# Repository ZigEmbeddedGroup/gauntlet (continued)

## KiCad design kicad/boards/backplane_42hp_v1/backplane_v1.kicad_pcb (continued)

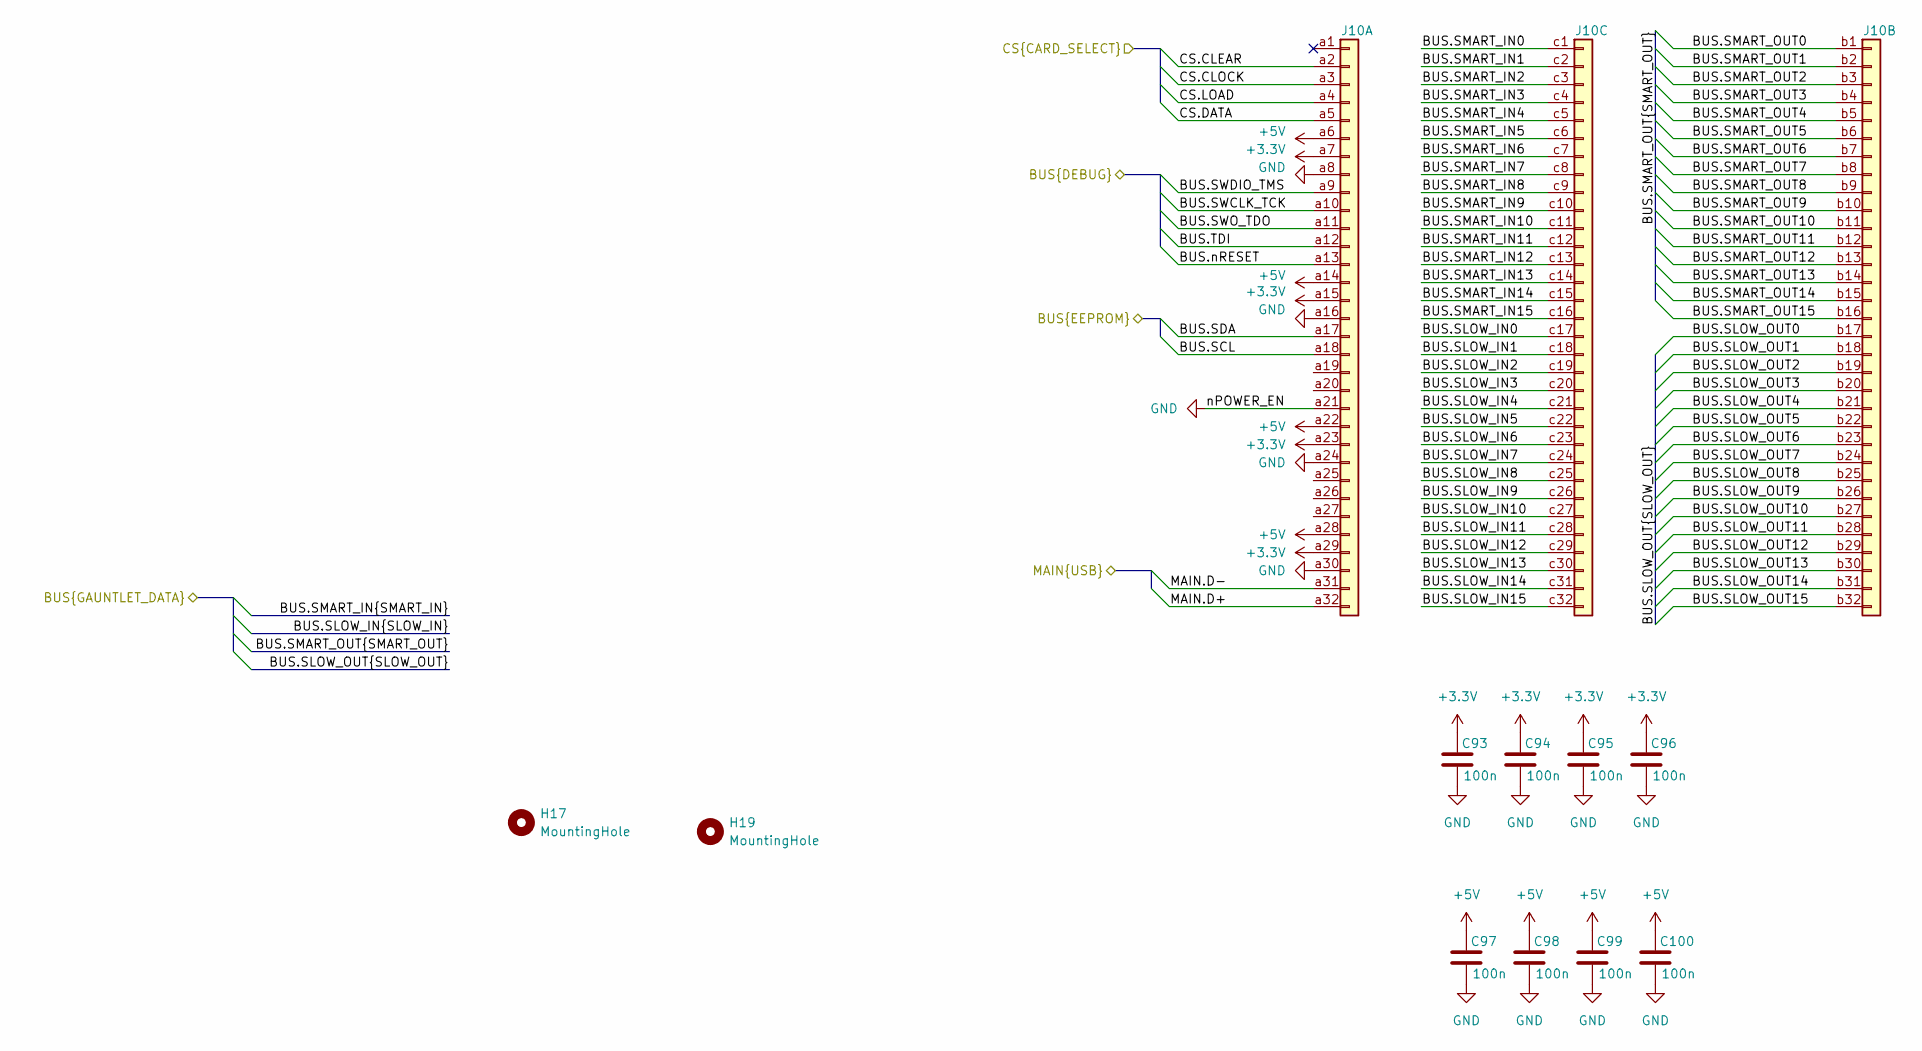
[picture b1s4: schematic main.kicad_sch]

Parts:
C93, C94, C95, C96, C97, C98, C99, C100: 100n; C_0603_1608Metric
H17, H19: MountingHole; MountingHole_3.2mm_M3
J10: DIN41612_03x32_C_Split; DIN41612_C_3x32_Female_Vertical_THT

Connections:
+3.3V: C93.1, C94.1, C95.1, C96.1, J10.a7, J10.a15, J10.a23, J10.a29; also elsewhere on the board
+5V: C97.1, C98.1, C99.1, C100.1, J10.a6, J10.a14, J10.a22, J10.a28; also elsewhere on the board
/BUS.SCL: J10.a18; also elsewhere on the board
/BUS.SDA: J10.a17; also elsewhere on the board
/BUS.SLOW_IN0: J10.c17; also elsewhere on the board
/BUS.SLOW_IN1: J10.c18; also elsewhere on the board
/BUS.SLOW_IN2: J10.c19; also elsewhere on the board
/BUS.SLOW_IN3: J10.c20; also elsewhere on the board
/BUS.SLOW_IN4: J10.c21; also elsewhere on the board
/BUS.SLOW_IN5: J10.c22; also elsewhere on the board
/BUS.SLOW_IN6: J10.c23; also elsewhere on the board
/BUS.SLOW_IN7: J10.c24; also elsewhere on the board
/BUS.SLOW_IN8: J10.c25; also elsewhere on the board
/BUS.SLOW_IN9: J10.c26; also elsewhere on the board
/BUS.SLOW_IN10: J10.c27; also elsewhere on the board
/BUS.SLOW_IN11: J10.c28; also elsewhere on the board
/BUS.SLOW_IN12: J10.c29; also elsewhere on the board
/BUS.SLOW_IN13: J10.c30; also elsewhere on the board
/BUS.SLOW_IN14: J10.c31; also elsewhere on the board
/BUS.SLOW_IN15: J10.c32; also elsewhere on the board
/BUS.SLOW_OUT0: J10.b17; also elsewhere on the board
/BUS.SLOW_OUT1: J10.b18; also elsewhere on the board
/BUS.SLOW_OUT2: J10.b19; also elsewhere on the board
/BUS.SLOW_OUT3: J10.b20; also elsewhere on the board
/BUS.SLOW_OUT4: J10.b21; also elsewhere on the board
/BUS.SLOW_OUT5: J10.b22; also elsewhere on the board
/BUS.SLOW_OUT6: J10.b23; also elsewhere on the board
/BUS.SLOW_OUT7: J10.b24; also elsewhere on the board
/BUS.SLOW_OUT8: J10.b25; also elsewhere on the board
/BUS.SLOW_OUT9: J10.b26; also elsewhere on the board
/BUS.SLOW_OUT10: J10.b27; also elsewhere on the board
/BUS.SLOW_OUT11: J10.b28; also elsewhere on the board
/BUS.SLOW_OUT12: J10.b29; also elsewhere on the board
/BUS.SLOW_OUT13: J10.b30; also elsewhere on the board
/BUS.SLOW_OUT14: J10.b31; also elsewhere on the board
/BUS.SLOW_OUT15: J10.b32; also elsewhere on the board
/BUS.SMART_IN0: J10.c1; also elsewhere on the board
/BUS.SMART_IN1: J10.c2; also elsewhere on the board
/BUS.SMART_IN2: J10.c3; also elsewhere on the board
/BUS.SMART_IN3: J10.c4; also elsewhere on the board
/BUS.SMART_IN4: J10.c5; also elsewhere on the board
/BUS.SMART_IN5: J10.c6; also elsewhere on the board
/BUS.SMART_IN6: J10.c7; also elsewhere on the board
/BUS.SMART_IN7: J10.c8; also elsewhere on the board
/BUS.SMART_IN8: J10.c9; also elsewhere on the board
/BUS.SMART_IN9: J10.c10; also elsewhere on the board
/BUS.SMART_IN10: J10.c11; also elsewhere on the board
/BUS.SMART_IN11: J10.c12; also elsewhere on the board
/BUS.SMART_IN12: J10.c13; also elsewhere on the board
/BUS.SMART_IN13: J10.c14; also elsewhere on the board
/BUS.SMART_IN14: J10.c15; also elsewhere on the board
/BUS.SMART_IN15: J10.c16; also elsewhere on the board
/BUS.SMART_OUT0: J10.b1; also elsewhere on the board
/BUS.SMART_OUT1: J10.b2; also elsewhere on the board
/BUS.SMART_OUT2: J10.b3; also elsewhere on the board
/BUS.SMART_OUT3: J10.b4; also elsewhere on the board
/BUS.SMART_OUT4: J10.b5; also elsewhere on the board
/BUS.SMART_OUT5: J10.b6; also elsewhere on the board
/BUS.SMART_OUT6: J10.b7; also elsewhere on the board
/BUS.SMART_OUT7: J10.b8; also elsewhere on the board
/BUS.SMART_OUT8: J10.b9; also elsewhere on the board
/BUS.SMART_OUT9: J10.b10; also elsewhere on the board
/BUS.SMART_OUT10: J10.b11; also elsewhere on the board
/BUS.SMART_OUT11: J10.b12; also elsewhere on the board
/BUS.SMART_OUT12: J10.b13; also elsewhere on the board
/BUS.SMART_OUT13: J10.b14; also elsewhere on the board
/BUS.SMART_OUT14: J10.b15; also elsewhere on the board
/BUS.SMART_OUT15: J10.b16; also elsewhere on the board
/BUS.SWCLK_TCK: J10.a10; also elsewhere on the board
/BUS.SWDIO_TMS: J10.a9; also elsewhere on the board
/BUS.SWO_TDO: J10.a11; also elsewhere on the board
/BUS.TDI: J10.a12; also elsewhere on the board
/BUS.nRESET: J10.a13; also elsewhere on the board
/CS.CLEAR: J10.a2; also elsewhere on the board
/CS.CLOCK: J10.a3; also elsewhere on the board
/CS.DATA: J10.a5; also elsewhere on the board
/CS.LOAD: J10.a4; also elsewhere on the board
/MAIN.D+: J10.a32; also elsewhere on the board
/MAIN.D-: J10.a31; also elsewhere on the board
GND: C93.2, C94.2, C95.2, C96.2, C97.2, C98.2, C99.2, C100.2, J10.a8, J10.a16, J10.a21, J10.a24, J10.a30; also elsewhere on the board

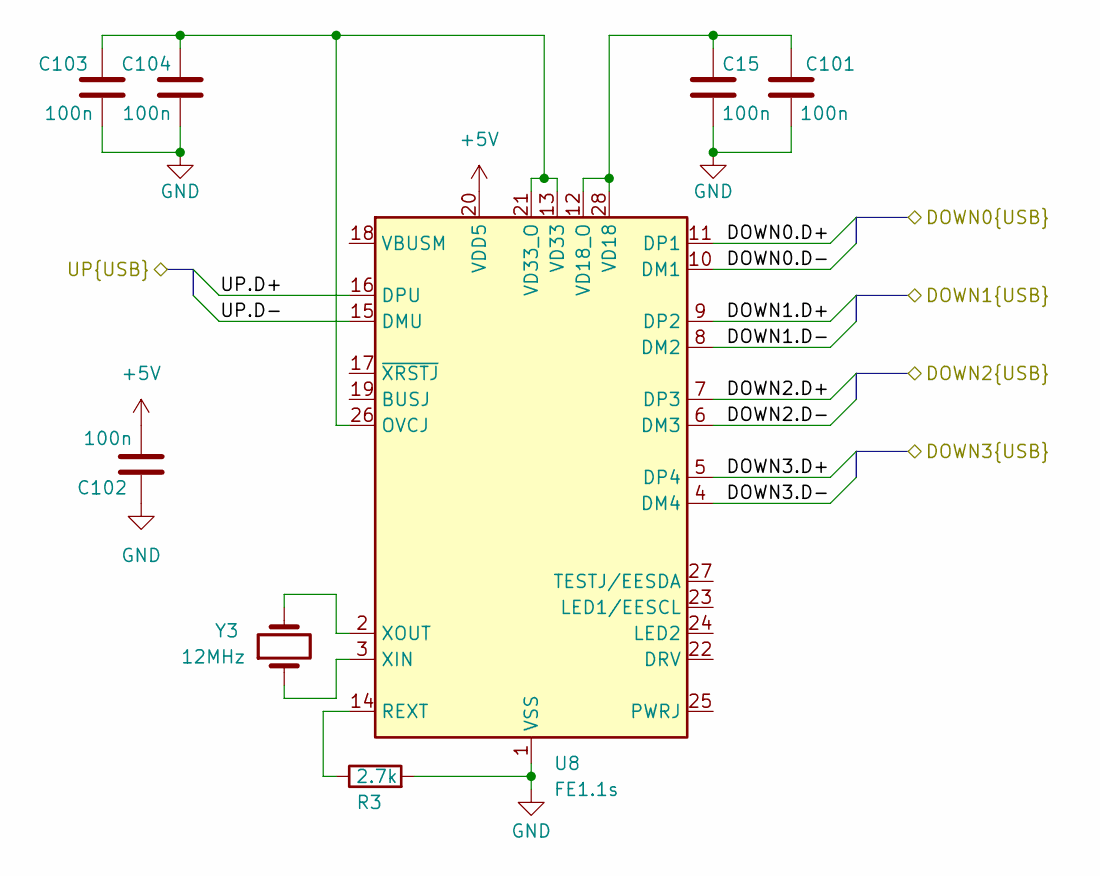
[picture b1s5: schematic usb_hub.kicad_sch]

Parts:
C15, C101, C102, C103, C104: 100n
R3: 2.7k
U8: FE1.1s; SSOP-28_3.9x9.9mm_P0.635mm
Y3: 12MHz

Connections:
+5V: C102.1, U8.20 (VDD5); also elsewhere on the board
/MAIN.D+: U8.16 (DPU); also elsewhere on the board
/MAIN.D-: U8.15 (DMU); also elsewhere on the board
/USB Hubs/USB Hub/DOWN0.D+: U8.11 (DP1); also elsewhere on the board
/USB Hubs/USB Hub/DOWN0.D-: U8.10 (DM1); also elsewhere on the board
/USB Hubs/USB Hub/DOWN1.D+: U8.9 (DP2); also elsewhere on the board
/USB Hubs/USB Hub/DOWN1.D-: U8.8 (DM2); also elsewhere on the board
/USB Hubs/USB Hub/DOWN2.D+: U8.7 (DP3)
/USB Hubs/USB Hub/DOWN2.D-: U8.6 (DM3)
/USB Hubs/USB Hub/DOWN3.D+: U8.5 (DP4)
/USB Hubs/USB Hub/DOWN3.D-: U8.4 (DM4)
GND: C15.1, C101.1, C102.2, C103.1, C104.1, R3.2, U8.1 (VSS); also elsewhere on the board
unnamed: U8.13 (VD33), U8.21 (VD33_O), U8.26 (OVCJ)
unnamed: U8.12 (VD18_O), U8.28 (VD18)

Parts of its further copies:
U9, U10: FE1.1s; SSOP-28_3.9x9.9mm_P0.635mm

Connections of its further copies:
+5V: U9.20 (VDD5), U10.20 (VDD5); also elsewhere on the board
/USB0.D+: U9.5 (DP4); also elsewhere on the board
/USB0.D-: U9.4 (DM4); also elsewhere on the board
/USB1.D+: U9.7 (DP3); also elsewhere on the board
/USB1.D-: U9.6 (DM3); also elsewhere on the board
/USB2.D+: U9.9 (DP2); also elsewhere on the board
/USB2.D-: U9.8 (DM2); also elsewhere on the board
/USB3.D+: U9.11 (DP1); also elsewhere on the board
/USB3.D-: U9.10 (DM1); also elsewhere on the board
/USB4.D+: U10.5 (DP4); also elsewhere on the board
/USB4.D-: U10.4 (DM4); also elsewhere on the board
/USB5.D+: U10.7 (DP3); also elsewhere on the board
/USB5.D-: U10.6 (DM3); also elsewhere on the board
/USB6.D+: U10.9 (DP2); also elsewhere on the board
/USB6.D-: U10.8 (DM2); also elsewhere on the board
/USB7.D+: U10.11 (DP1); also elsewhere on the board
/USB7.D-: U10.10 (DM1); also elsewhere on the board
/USB Hubs/USB Hub/DOWN0.D+: U9.16 (DPU); also elsewhere on the board
/USB Hubs/USB Hub/DOWN0.D-: U9.15 (DMU); also elsewhere on the board
/USB Hubs/USB Hub/DOWN1.D+: U10.16 (DPU); also elsewhere on the board
/USB Hubs/USB Hub/DOWN1.D-: U10.15 (DMU); also elsewhere on the board
GND: U9.1 (VSS), U10.1 (VSS); also elsewhere on the board
unnamed: U9.13 (VD33), U9.21 (VD33_O), U9.26 (OVCJ)
unnamed: U9.12 (VD18_O), U9.28 (VD18)
unnamed: U10.13 (VD33), U10.21 (VD33_O), U10.26 (OVCJ)
unnamed: U10.12 (VD18_O), U10.28 (VD18)

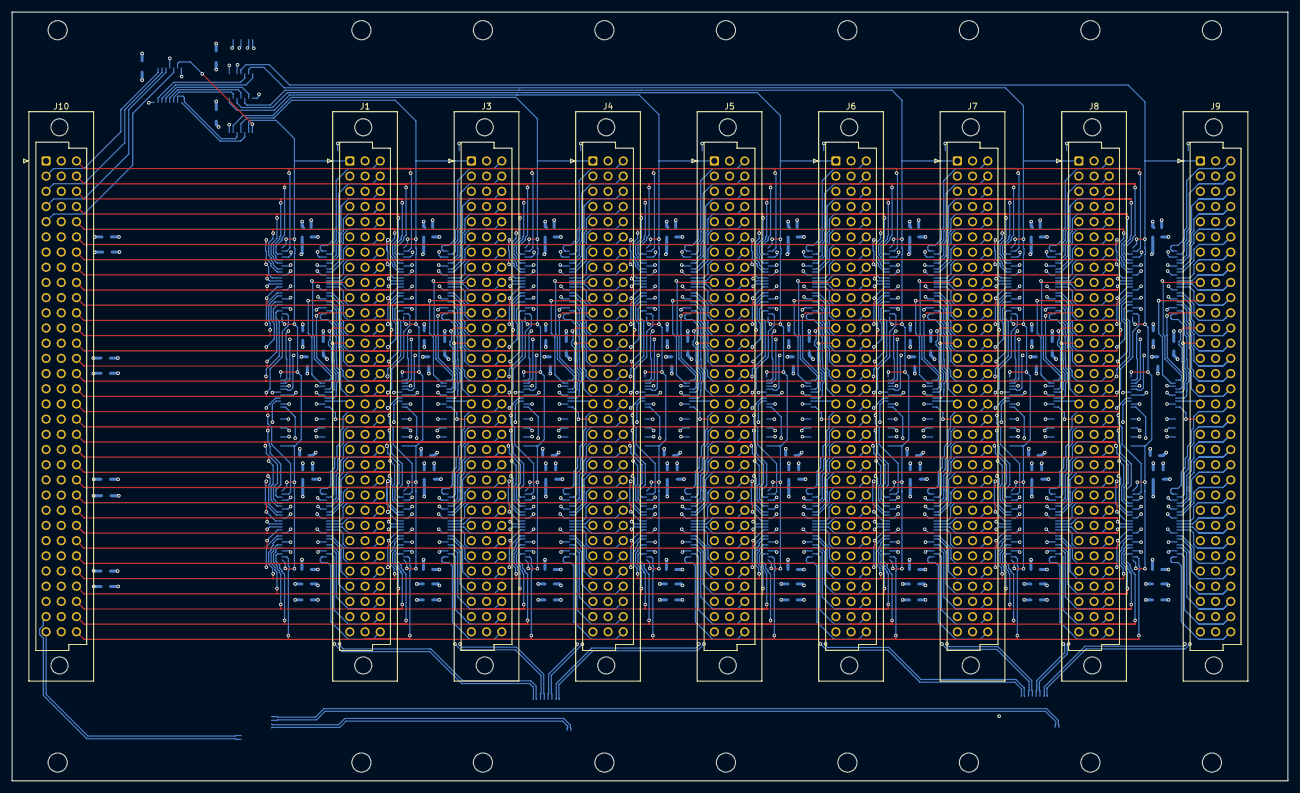
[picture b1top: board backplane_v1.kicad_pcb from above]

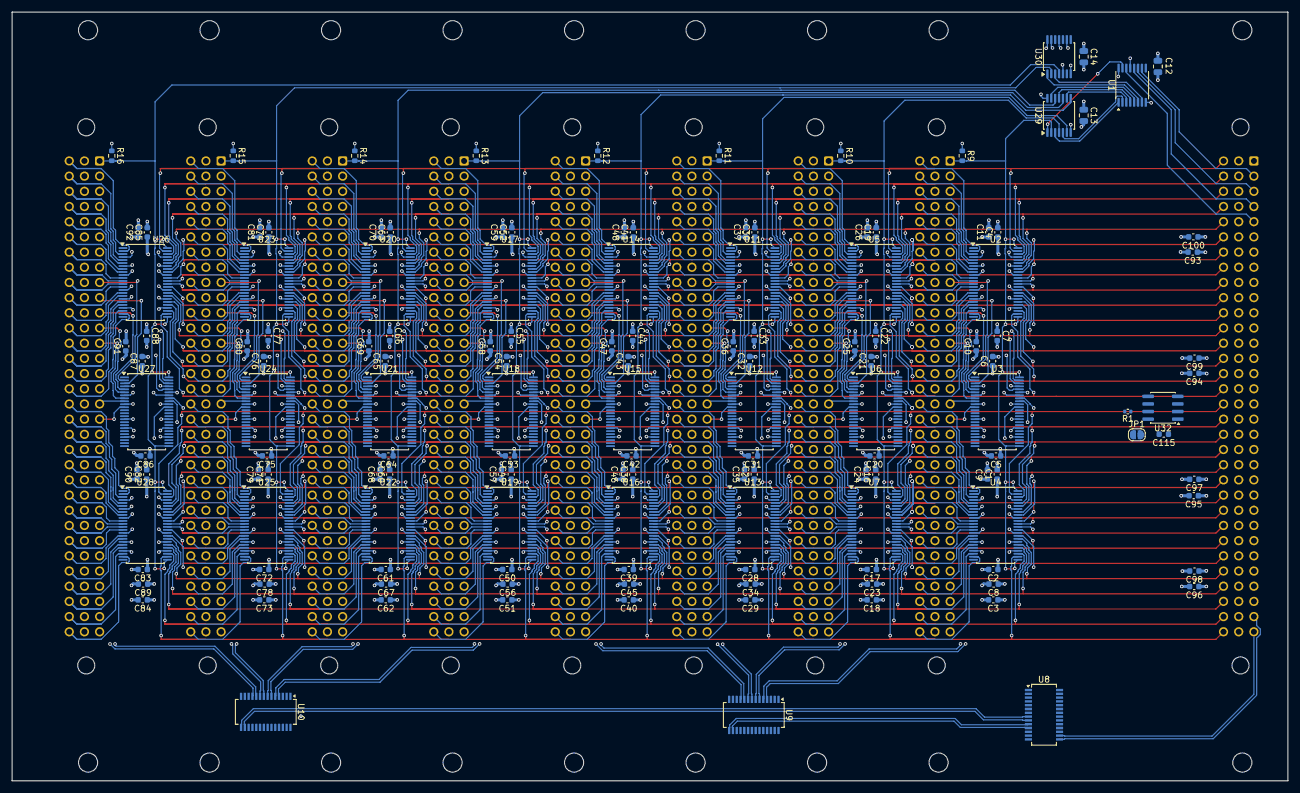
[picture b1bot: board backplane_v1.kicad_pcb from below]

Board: 6 copper layers, 213.4 x 128.6 mm, 168 parts (141 on the bottom side), 435 nets.

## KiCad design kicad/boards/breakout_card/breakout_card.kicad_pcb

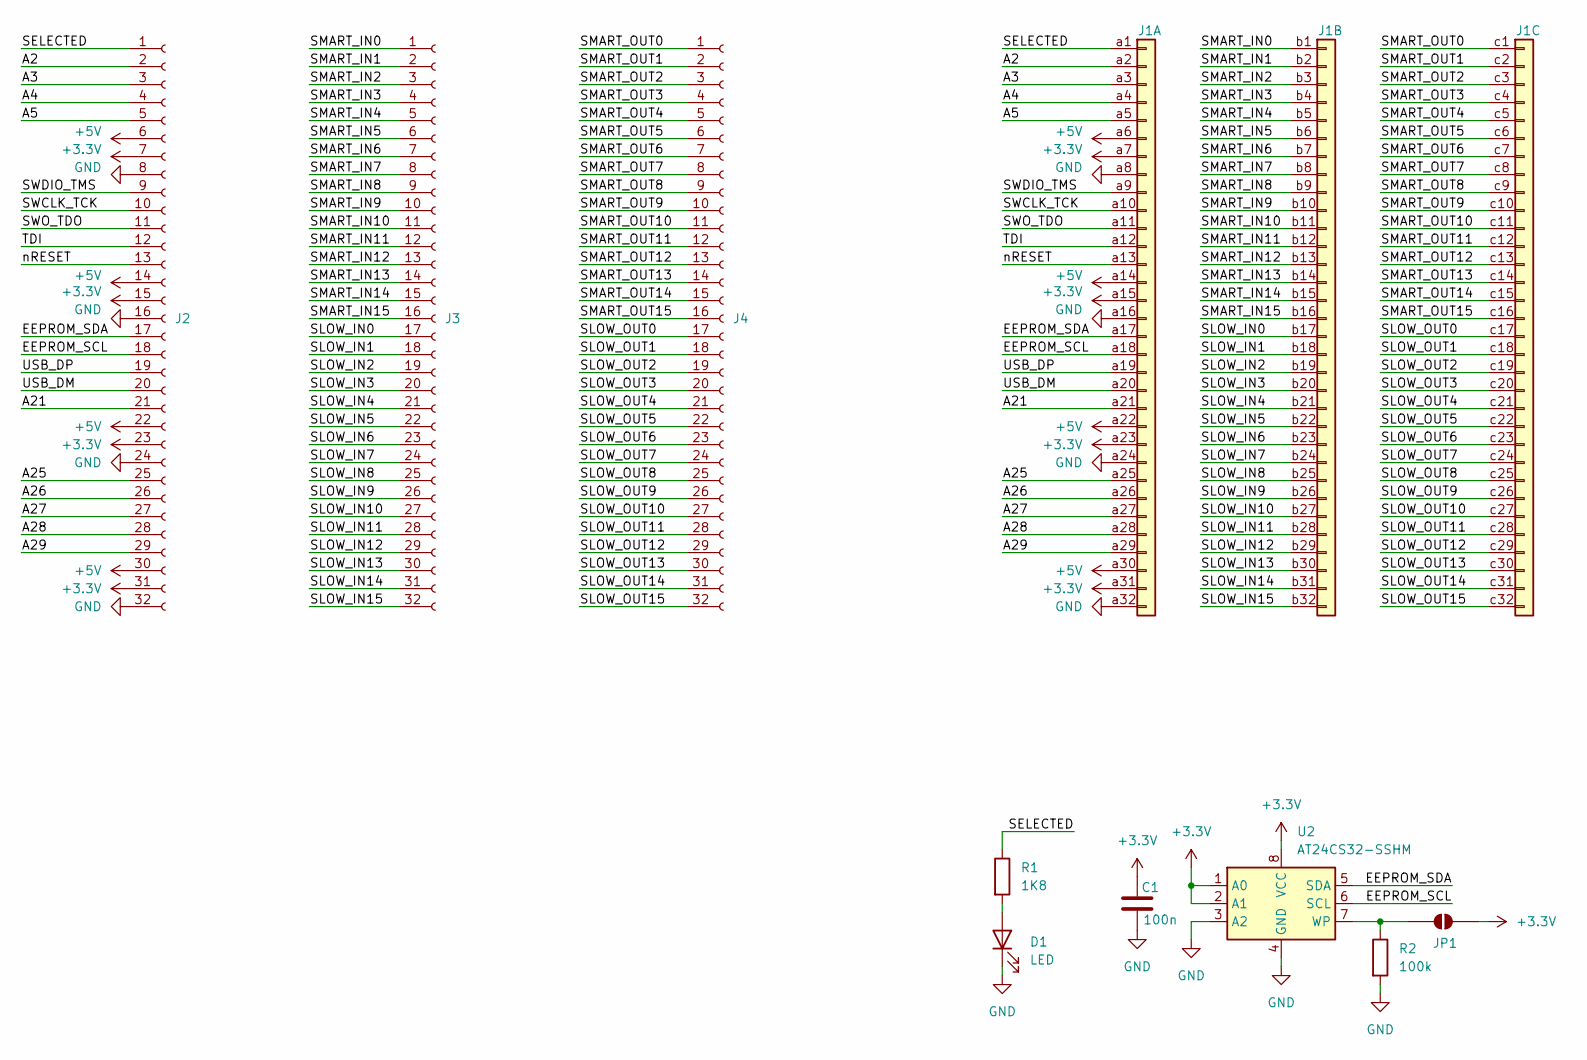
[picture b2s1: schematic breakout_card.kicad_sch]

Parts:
C1: 100n; C_0603_1608Metric
D1: LED; LED_Kingbright_APDA3020VBCD
J1: DIN41612_03x32_C_Split; DIN41612_C_3x32_Male_Horizontal_THT
J2, J3, J4: Conn_01x32_Socket; PinHeader_1x32_P2.54mm_Vertical
JP1: SolderJumper_2_Open; SolderJumper-2_P1.3mm_Open_RoundedPad1.0x1.5mm
R1: 1K8; R_0603_1608Metric_Pad0.98x0.95mm_HandSolder
R2: 100k; R_0603_1608Metric
U2: AT24CS32-SSHM; SOIC-8_3.9x4.9mm_P1.27mm

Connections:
+3.3V: C1.1, J1.a7, J1.a15, J1.a23, J1.a31, J2.7, J2.15, J2.23, J2.31, JP1.2 (B), U2.1 (A0), U2.2 (A1), U2.8 (VCC)
+5V: J1.a6, J1.a14, J1.a22, J1.a30, J2.6, J2.14, J2.22, J2.30
/A2: J1.a2, J2.2
/A3: J1.a3, J2.3
/A4: J1.a4, J2.4
/A5: J1.a5, J2.5
/A21: J1.a21, J2.21
/A25: J1.a25, J2.25
/A26: J1.a26, J2.26
/A27: J1.a27, J2.27
/A28: J1.a28, J2.28
/A29: J1.a29, J2.29
/EEPROM_SCL: J1.a18, J2.18, U2.6 (SCL)
/EEPROM_SDA: J1.a17, J2.17, U2.5 (SDA)
/SELECTED: J1.a1, J2.1, R1.1
/SLOW_IN0: J1.b17, J3.17
/SLOW_IN1: J1.b18, J3.18
/SLOW_IN2: J1.b19, J3.19
/SLOW_IN3: J1.b20, J3.20
/SLOW_IN4: J1.b21, J3.21
/SLOW_IN5: J1.b22, J3.22
/SLOW_IN6: J1.b23, J3.23
/SLOW_IN7: J1.b24, J3.24
/SLOW_IN8: J1.b25, J3.25
/SLOW_IN9: J1.b26, J3.26
/SLOW_IN10: J1.b27, J3.27
/SLOW_IN11: J1.b28, J3.28
/SLOW_IN12: J1.b29, J3.29
/SLOW_IN13: J1.b30, J3.30
/SLOW_IN14: J1.b31, J3.31
/SLOW_IN15: J1.b32, J3.32
/SLOW_OUT0: J1.c17, J4.17
/SLOW_OUT1: J1.c18, J4.18
/SLOW_OUT2: J1.c19, J4.19
/SLOW_OUT3: J1.c20, J4.20
/SLOW_OUT4: J1.c21, J4.21
/SLOW_OUT5: J1.c22, J4.22
/SLOW_OUT6: J1.c23, J4.23
/SLOW_OUT7: J1.c24, J4.24
/SLOW_OUT8: J1.c25, J4.25
/SLOW_OUT9: J1.c26, J4.26
/SLOW_OUT10: J1.c27, J4.27
/SLOW_OUT11: J1.c28, J4.28
/SLOW_OUT12: J1.c29, J4.29
/SLOW_OUT13: J1.c30, J4.30
/SLOW_OUT14: J1.c31, J4.31
/SLOW_OUT15: J1.c32, J4.32
/SMART_IN0: J1.b1, J3.1
/SMART_IN1: J1.b2, J3.2
/SMART_IN2: J1.b3, J3.3
/SMART_IN3: J1.b4, J3.4
/SMART_IN4: J1.b5, J3.5
/SMART_IN5: J1.b6, J3.6
/SMART_IN6: J1.b7, J3.7
/SMART_IN7: J1.b8, J3.8
/SMART_IN8: J1.b9, J3.9
/SMART_IN9: J1.b10, J3.10
/SMART_IN10: J1.b11, J3.11
/SMART_IN11: J1.b12, J3.12
/SMART_IN12: J1.b13, J3.13
/SMART_IN13: J1.b14, J3.14
/SMART_IN14: J1.b15, J3.15
/SMART_IN15: J1.b16, J3.16
/SMART_OUT0: J1.c1, J4.1
/SMART_OUT1: J1.c2, J4.2
/SMART_OUT2: J1.c3, J4.3
/SMART_OUT3: J1.c4, J4.4
/SMART_OUT4: J1.c5, J4.5
/SMART_OUT5: J1.c6, J4.6
/SMART_OUT6: J1.c7, J4.7
/SMART_OUT7: J1.c8, J4.8
/SMART_OUT8: J1.c9, J4.9
/SMART_OUT9: J1.c10, J4.10
/SMART_OUT10: J1.c11, J4.11
/SMART_OUT11: J1.c12, J4.12
/SMART_OUT12: J1.c13, J4.13
/SMART_OUT13: J1.c14, J4.14
/SMART_OUT14: J1.c15, J4.15
/SMART_OUT15: J1.c16, J4.16
/SWCLK_TCK: J1.a10, J2.10
/SWDIO_TMS: J1.a9, J2.9
/SWO_TDO: J1.a11, J2.11
/TDI: J1.a12, J2.12
/USB_DM: J1.a20, J2.20
/USB_DP: J1.a19, J2.19
/nRESET: J1.a13, J2.13
GND: C1.2, D1.1 (K), J1.a8, J1.a16, J1.a24, J1.a32, J2.8, J2.16, J2.24, J2.32, R2.2, U2.3 (A2), U2.4 (GND)
unnamed: D1.2 (A), R1.2
unnamed: JP1.1 (A), R2.1, U2.7 (WP)

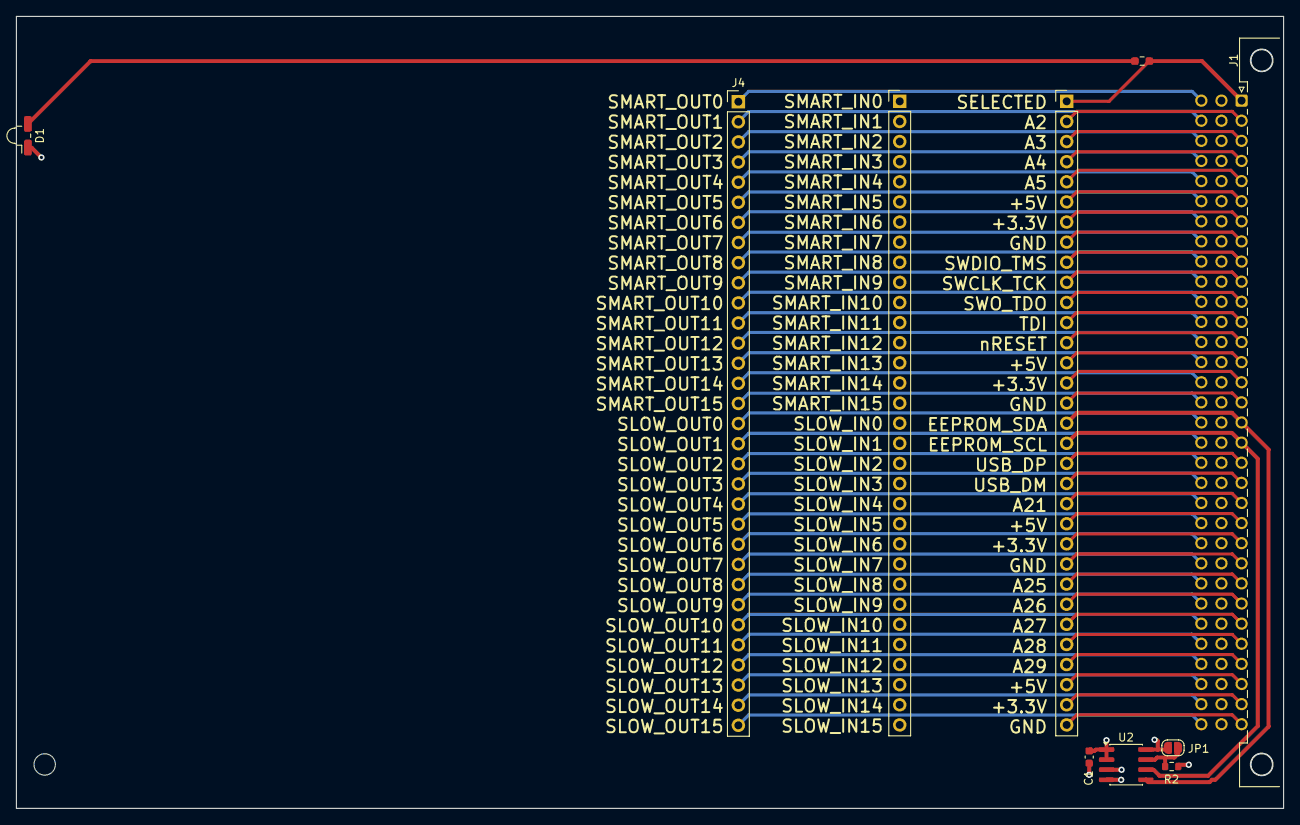
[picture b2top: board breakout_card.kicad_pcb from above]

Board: 4 copper layers, 160.0 x 100.0 mm, 13 parts (0 on the bottom side), 89 nets.

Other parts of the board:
MH2, MH3, MH4: MountingHole_2.7mm_M2.5_DIN965

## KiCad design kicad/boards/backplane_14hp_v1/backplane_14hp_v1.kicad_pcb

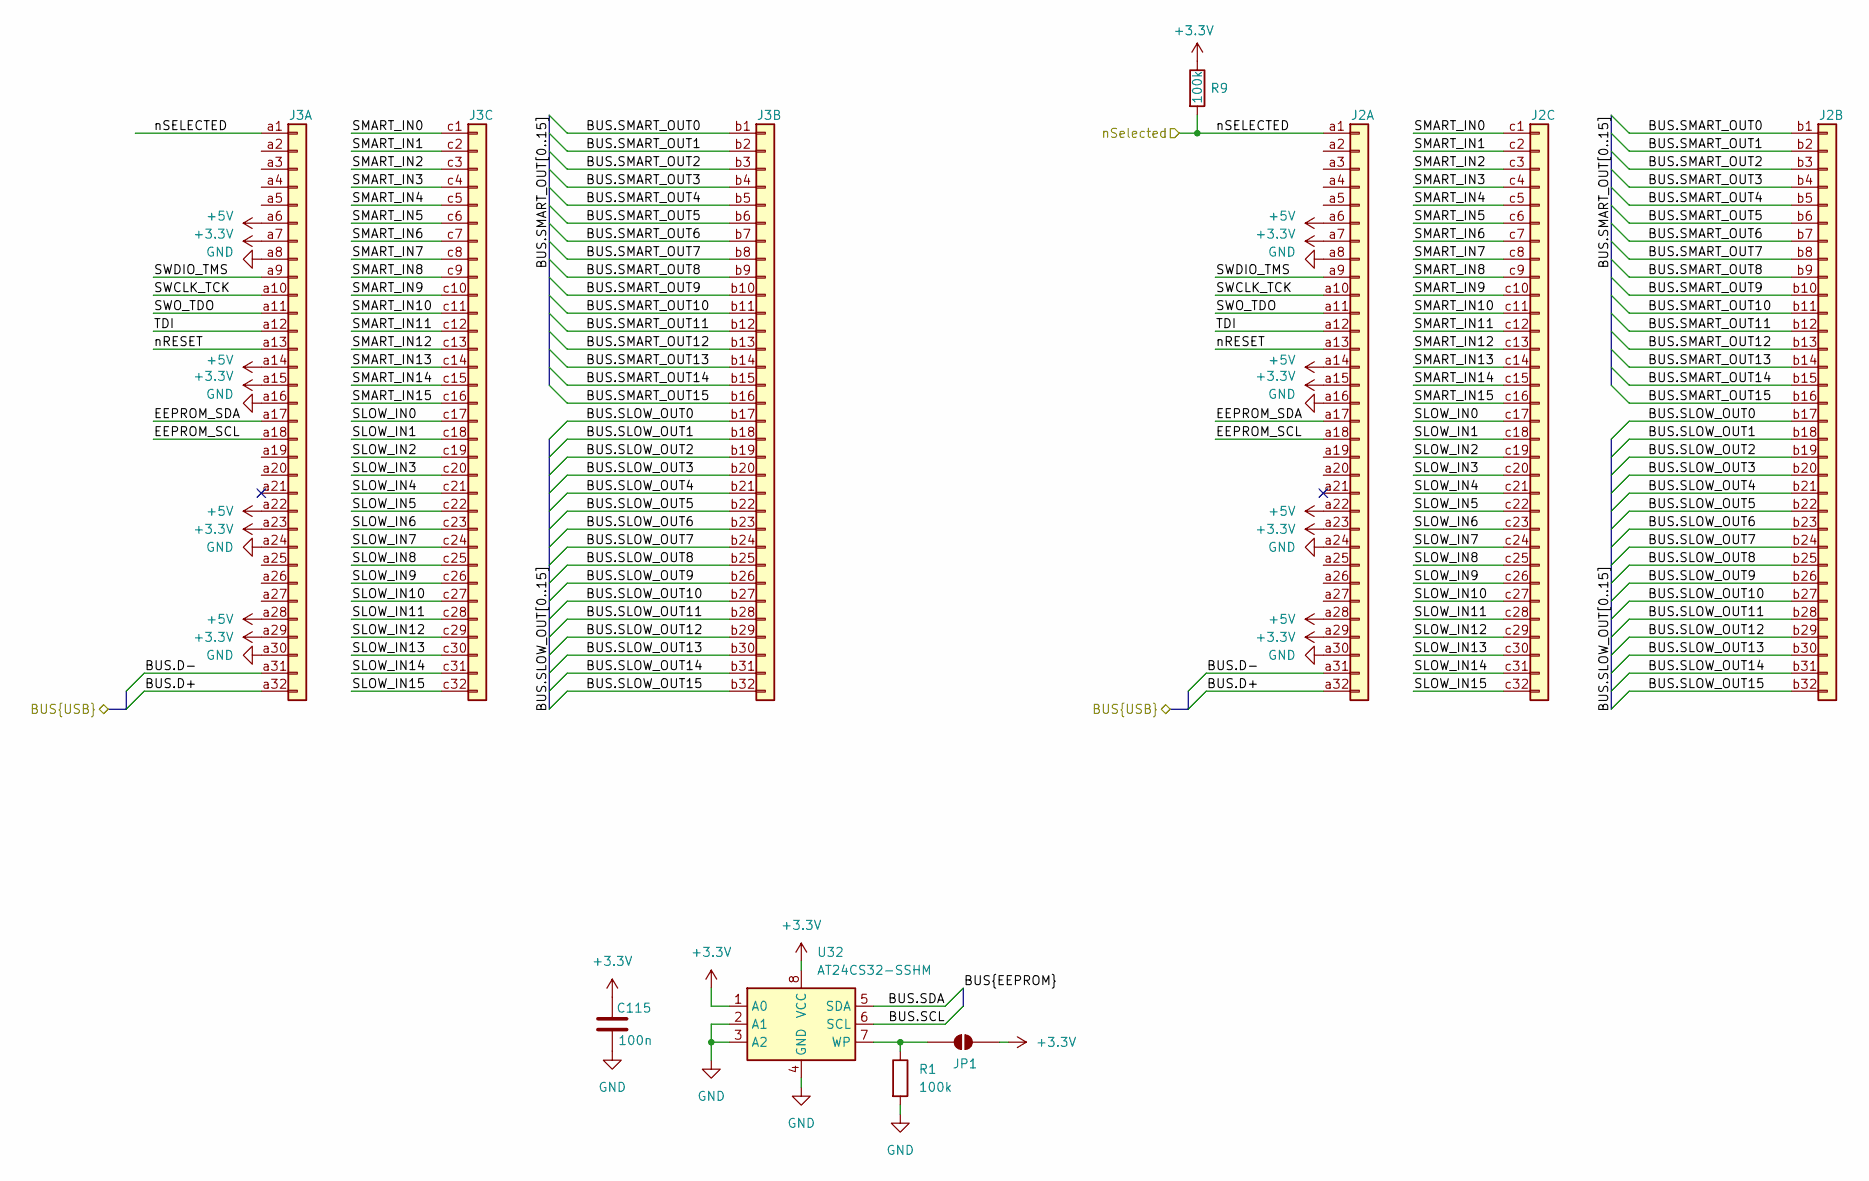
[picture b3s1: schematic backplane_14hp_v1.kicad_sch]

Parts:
C115: 100n; C_0603_1608Metric
J2, J3: DIN41612_03x32_C_Split; DIN41612_C_3x32_Female_Vertical_THT
JP1: SolderJumper_2_Open; SolderJumper-2_P1.3mm_Open_RoundedPad1.0x1.5mm
R1, R9: 100k; R_0603_1608Metric
U32: AT24CS32-SSHM; SOIC-8_3.9x4.9mm_P1.27mm

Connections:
+3.3V: C115.1, J2.a7, J2.a15, J2.a23, J2.a29, J3.a7, J3.a15, J3.a23, J3.a29, JP1.2 (B), R9.1, U32.1 (A0), U32.8 (VCC)
+5V: J2.a6, J2.a14, J2.a22, J2.a28, J3.a6, J3.a14, J3.a22, J3.a28
/BUS.D+: J2.a32, J3.a32
/BUS.D-: J2.a31, J3.a31
/BUS.SCL: U32.6 (SCL)
/BUS.SDA: U32.5 (SDA)
/BUS.SLOW_OUT0: J2.b17, J3.b17
/BUS.SLOW_OUT1: J2.b18, J3.b18
/BUS.SLOW_OUT2: J2.b19, J3.b19
/BUS.SLOW_OUT3: J2.b20, J3.b20
/BUS.SLOW_OUT4: J2.b21, J3.b21
/BUS.SLOW_OUT5: J2.b22, J3.b22
/BUS.SLOW_OUT6: J2.b23, J3.b23
/BUS.SLOW_OUT7: J2.b24, J3.b24
/BUS.SLOW_OUT8: J2.b25, J3.b25
/BUS.SLOW_OUT9: J2.b26, J3.b26
/BUS.SLOW_OUT10: J2.b27, J3.b27
/BUS.SLOW_OUT11: J2.b28, J3.b28
/BUS.SLOW_OUT12: J2.b29, J3.b29
/BUS.SLOW_OUT13: J2.b30, J3.b30
/BUS.SLOW_OUT14: J2.b31, J3.b31
/BUS.SLOW_OUT15: J2.b32, J3.b32
/BUS.SMART_OUT0: J2.b1, J3.b1
/BUS.SMART_OUT1: J2.b2, J3.b2
/BUS.SMART_OUT2: J2.b3, J3.b3
/BUS.SMART_OUT3: J2.b4, J3.b4
/BUS.SMART_OUT4: J2.b5, J3.b5
/BUS.SMART_OUT5: J2.b6, J3.b6
/BUS.SMART_OUT6: J2.b7, J3.b7
/BUS.SMART_OUT7: J2.b8, J3.b8
/BUS.SMART_OUT8: J2.b9, J3.b9
/BUS.SMART_OUT9: J2.b10, J3.b10
/BUS.SMART_OUT10: J2.b11, J3.b11
/BUS.SMART_OUT11: J2.b12, J3.b12
/BUS.SMART_OUT12: J2.b13, J3.b13
/BUS.SMART_OUT13: J2.b14, J3.b14
/BUS.SMART_OUT14: J2.b15, J3.b15
/BUS.SMART_OUT15: J2.b16, J3.b16
/EEPROM_SCL: J2.a18, J3.a18
/EEPROM_SDA: J2.a17, J3.a17
/SLOW_IN0: J2.c17, J3.c17
/SLOW_IN1: J2.c18, J3.c18
/SLOW_IN2: J2.c19, J3.c19
/SLOW_IN3: J2.c20, J3.c20
/SLOW_IN4: J2.c21, J3.c21
/SLOW_IN5: J2.c22, J3.c22
/SLOW_IN6: J2.c23, J3.c23
/SLOW_IN7: J2.c24, J3.c24
/SLOW_IN8: J2.c25, J3.c25
/SLOW_IN9: J2.c26, J3.c26
/SLOW_IN10: J2.c27, J3.c27
/SLOW_IN11: J2.c28, J3.c28
/SLOW_IN12: J2.c29, J3.c29
/SLOW_IN13: J2.c30, J3.c30
/SLOW_IN14: J2.c31, J3.c31
/SLOW_IN15: J2.c32, J3.c32
/SMART_IN0: J2.c1, J3.c1
/SMART_IN1: J2.c2, J3.c2
/SMART_IN2: J2.c3, J3.c3
/SMART_IN3: J2.c4, J3.c4
/SMART_IN4: J2.c5, J3.c5
/SMART_IN5: J2.c6, J3.c6
/SMART_IN6: J2.c7, J3.c7
/SMART_IN7: J2.c8, J3.c8
/SMART_IN8: J2.c9, J3.c9
/SMART_IN9: J2.c10, J3.c10
/SMART_IN10: J2.c11, J3.c11
/SMART_IN11: J2.c12, J3.c12
/SMART_IN12: J2.c13, J3.c13
/SMART_IN13: J2.c14, J3.c14
/SMART_IN14: J2.c15, J3.c15
/SMART_IN15: J2.c16, J3.c16
/SWCLK_TCK: J2.a10, J3.a10
/SWDIO_TMS: J2.a9, J3.a9
/SWO_TDO: J2.a11, J3.a11
/TDI: J2.a12, J3.a12
/nRESET: J2.a13, J3.a13
/nSELECTED: J2.a1, J3.a1, R9.2
GND: C115.2, J2.a8, J2.a16, J2.a24, J2.a30, J3.a8, J3.a16, J3.a24, J3.a30, R1.2, U32.2 (A1), U32.3 (A2), U32.4 (GND)
unnamed: JP1.1 (A), R1.1, U32.7 (WP)

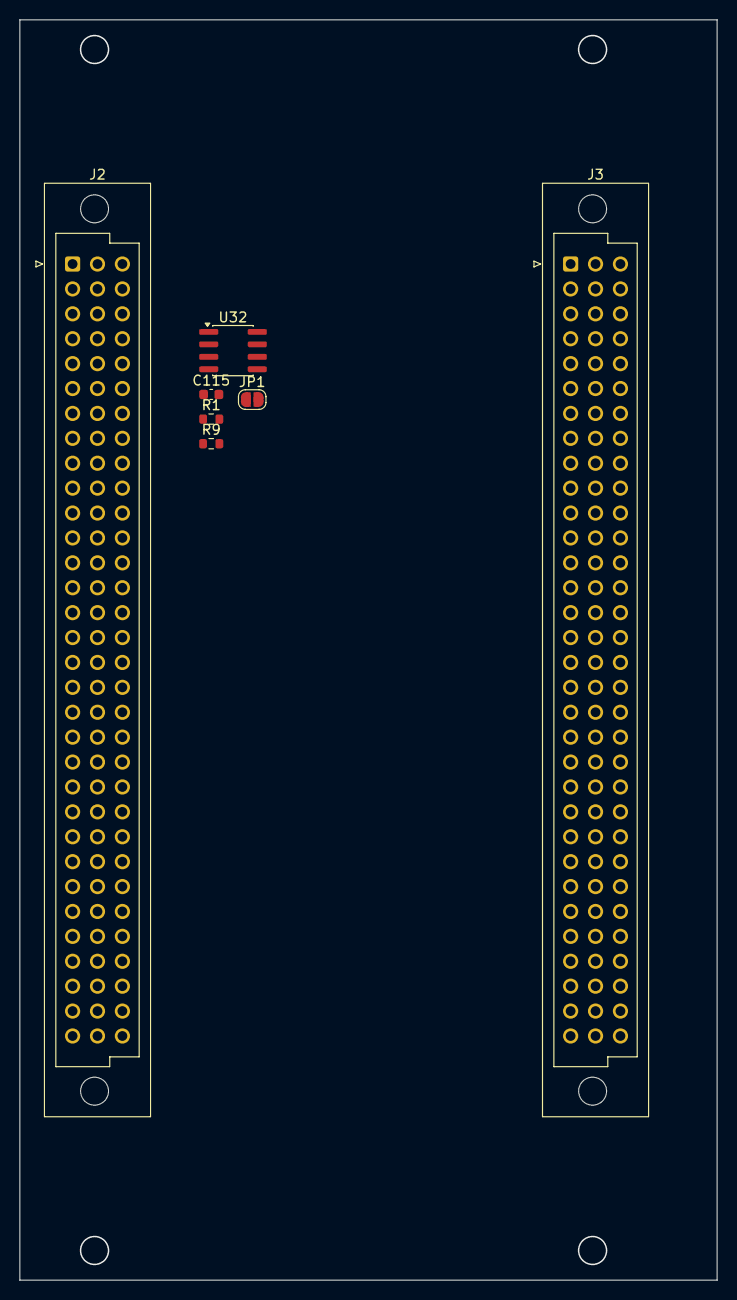
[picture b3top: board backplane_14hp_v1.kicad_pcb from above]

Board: 8 copper layers, 71.1 x 128.6 mm, 7 parts (0 on the bottom side), 78 nets.

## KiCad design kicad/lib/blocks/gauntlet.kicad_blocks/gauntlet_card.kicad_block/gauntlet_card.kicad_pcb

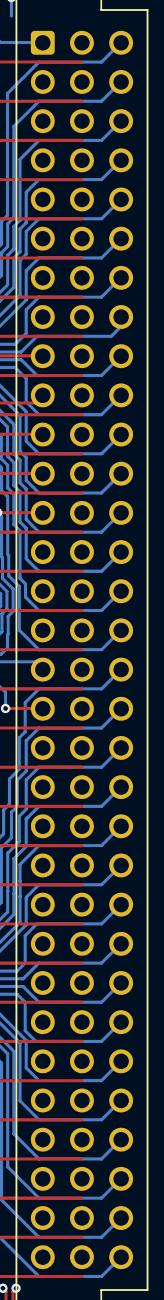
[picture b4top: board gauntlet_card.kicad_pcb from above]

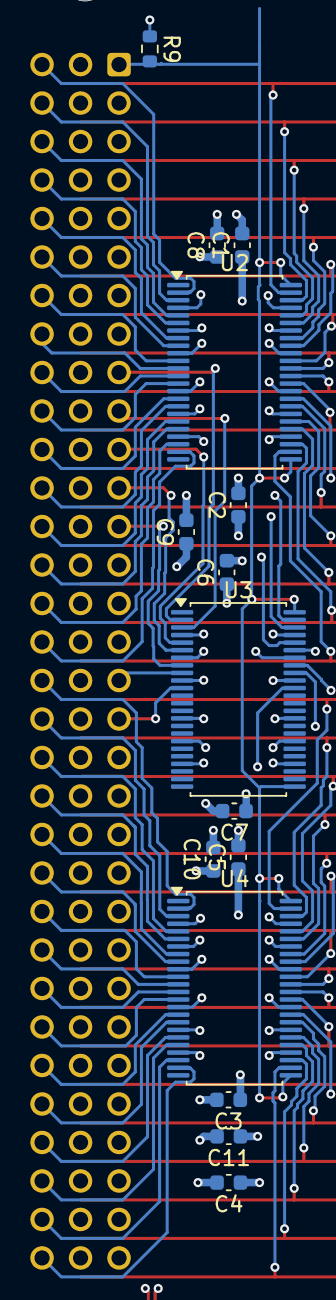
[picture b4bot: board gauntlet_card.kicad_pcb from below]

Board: 6 copper layers, 18 parts (15 on the bottom side), 4 nets.

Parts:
C1, C2, C3, C4, C5, C6, C7, C8, C9, C10, C11: 100n; C_0603_1608Metric
H1, H2: MountingHole; MountingHole_3.2mm_M3
J1: DIN41612_03x32_C_Split; DIN41612_C_3x32_Female_Vertical_THT
R9: 100k; R_0603_1608Metric
U2, U3, U4: SN74CB3Q16245; TSSOP-48_6.1x12.5mm_P0.5mm

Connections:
+3.3V: C1.1, C2.1, C3.1, C4.1, C5.1, C6.1, C7.1, J1.a7, J1.a15, J1.a23, J1.a29, R9.1, U2.7 (VCC), U2.18 (VCC), U2.31 (VCC), U2.42 (VCC), U3.7 (VCC), U3.18 (VCC), U3.31 (VCC), U3.42 (VCC), U4.7 (VCC), U4.18 (VCC), U4.31 (VCC), U4.42 (VCC)
+5V: C8.1, C9.1, C10.1, C11.1, J1.a6, J1.a14, J1.a22, J1.a28
/nSELECTED: R9.2, U2.25 (~OE2), U2.48 (~OE1), U3.25 (~OE2), U3.48 (~OE1), U4.25 (~OE2), U4.48 (~OE1)
GND: C1.2, C2.2, C3.2, C4.2, C5.2, C6.2, C7.2, C8.2, C9.2, C10.2, C11.2, J1.a8, J1.a16, J1.a24, J1.a30, U2.4 (GND), U2.10 (GND), U2.15 (GND), U2.21 (GND), U2.28 (GND), U2.34 (GND), U2.39 (GND), U2.45 (GND), U3.4 (GND), U3.10 (GND), U3.15 (GND), U3.21 (GND), U3.28 (GND), U3.34 (GND), U3.39 (GND), U3.45 (GND), U4.4 (GND), U4.10 (GND), U4.15 (GND), U4.21 (GND), U4.28 (GND), U4.34 (GND), U4.39 (GND), U4.45 (GND)

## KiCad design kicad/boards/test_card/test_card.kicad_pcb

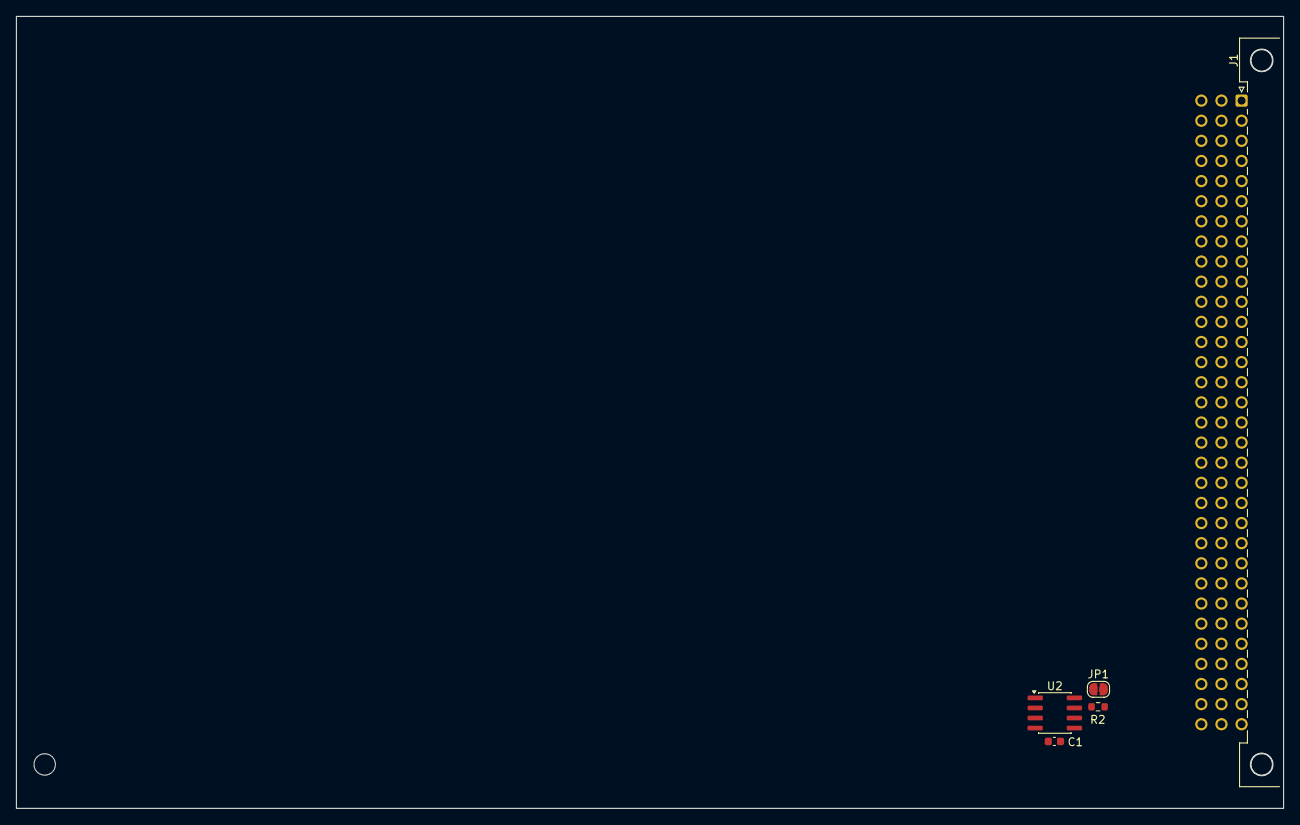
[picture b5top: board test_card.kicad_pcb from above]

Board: 2 copper layers, 160.0 x 100.0 mm, 8 parts (0 on the bottom side), 4 nets, no tracks yet.

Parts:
C1: 100n; C_0603_1608Metric
J1: DIN41612_03x32_C_Split; DIN41612_C_3x32_Male_Horizontal_THT
JP1: SolderJumper_2_Open; SolderJumper-2_P1.3mm_Open_RoundedPad1.0x1.5mm
MH2, MH3, MH4: MountingHole_2.7mm_M2.5_DIN965
R2: 100k; R_0603_1608Metric
U2: AT24CS32-SSHM; SOIC-8_3.9x4.9mm_P1.27mm

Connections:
+3.3V: C1.1, J1.a7, J1.a15, J1.a23, J1.a31, JP1.2 (B), U2.1 (A0), U2.2 (A1), U2.8 (VCC)
+5V: J1.a6, J1.a14, J1.a22, J1.a30
GND: C1.2, J1.a8, J1.a16, J1.a24, J1.a32, R2.2, U2.3 (A2), U2.4 (GND)
unnamed: JP1.1 (A), R2.1, U2.7 (WP)
